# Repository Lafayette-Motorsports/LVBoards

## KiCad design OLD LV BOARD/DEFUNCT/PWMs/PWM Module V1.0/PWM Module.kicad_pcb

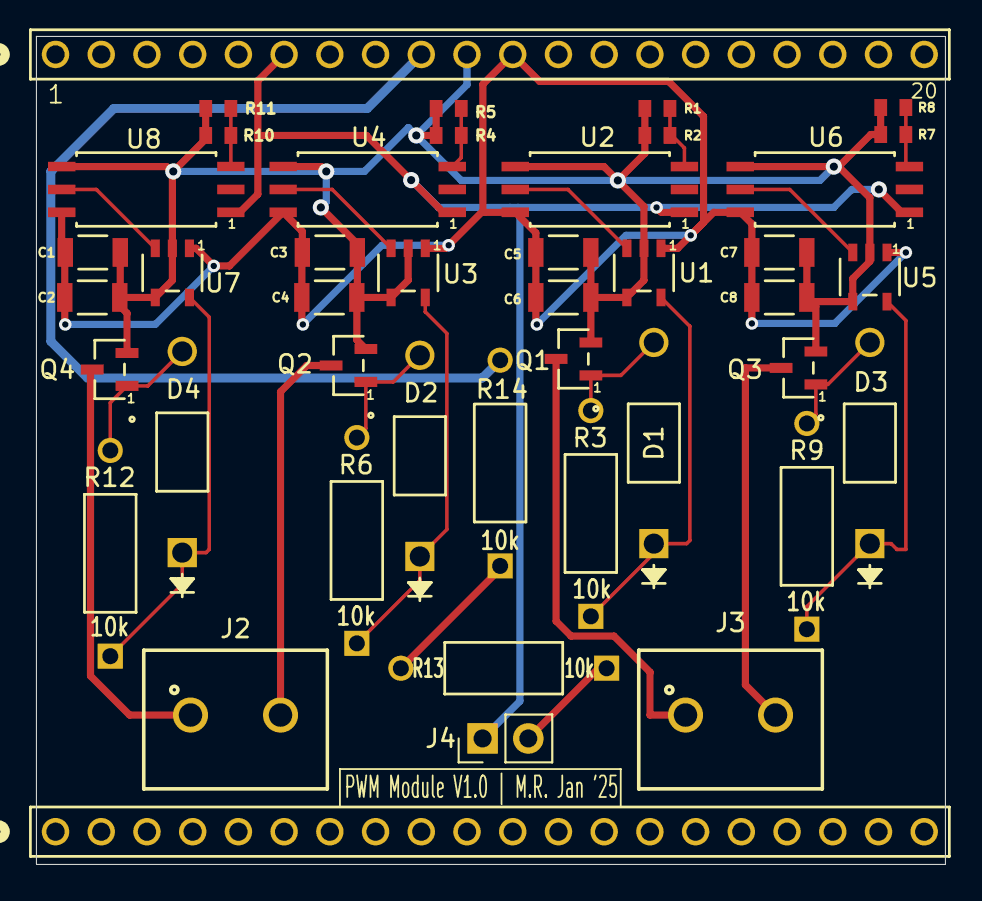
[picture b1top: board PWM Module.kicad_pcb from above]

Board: 2 copper layers, 50.5 x 46.0 mm, 43 parts (0 on the bottom side), 26 nets.

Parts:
C1, C2, C3, C4, C5, C6, C7, C8: 0.1u; CAP_CL31_SAM
D1, D2, D3, D4: 1N4001; DO-41_DIO
J2, J3: Conn_01x02_Pin; 691137710002
J4: Conn_01x02_Pin; PinHeader_1x02_P2.54mm_Vertical
J5, J5#2: PH1-20-UA; CONN_PH1-20-UA_ADM
Q1, Q2, Q3, Q4: DMN3404L-7; SOT23_DIO
R1, R2, R4, R5, R7, R8, R10, R11: 1k; STA_RMCF0603_STP
R3, R6, R9, R12, R13, R14: 10k; STA_CF14_STP
U1, U3, U5, U7: UCC27517DBVR; DBV5_TEX
U2, U4, U6, U8: TLP2745TP_E; SO6L_TOS

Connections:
GND: C1.2, C2.2, C3.2, C4.2, C5.2, C6.2, C7.2, C8.2, J5.10, Q1.2 (S), Q2.2 (S), Q3.2 (S), Q4.2 (S), R1.1, R2.1, R4.1, R5.1, R7.1, R8.1, R10.1, R11.1, U1.2 (GND), U1.4 (IN-), U2.4, U3.2 (GND), U3.4 (IN-), U4.4, U5.2 (GND), U5.4 (IN-), U6.4, U7.2 (GND), U7.4 (IN-), U8.4
unnamed: D1.2 (A), Q1.1 (G), R3.2
unnamed: D1.1 (K), R3.1, U1.5 (OUT)
unnamed: D2.2 (A), Q2.1 (G), R6.2
unnamed: D2.1 (K), R6.1, U3.5 (OUT)
unnamed: D3.2 (A), Q3.1 (G), R9.2
unnamed: D3.1 (K), R9.1, U5.5 (OUT)
unnamed: D4.2 (A), Q4.1 (G), R12.2
unnamed: D4.1 (K), R12.1, U7.5 (OUT)
unnamed: J2.1, Q4.3 (D)
unnamed: J2.2, Q2.3 (D)
unnamed: J3.1, Q1.3 (D)
unnamed: J3.2, Q3.3 (D)
unnamed: J4.1, J5.6, U2.1, U4.1, U6.1, U8.1
unnamed: J4.2, R13.1
unnamed: J5.9, R14.2
unnamed: R1.2, R2.2, U2.3
unnamed: R4.2, R5.2, U4.3
unnamed: R7.2, R8.2, U6.3
unnamed: R10.2, R11.2, U8.3
unnamed: R13.2, R14.1
unnamed: U1.3 (IN+), U2.5
unnamed: C1.1, C2.1, C3.1, C4.1, C5.1, C6.1, C7.1, C8.1, J5.11, U1.1 (VDD), U2.6, U3.1 (VDD), U4.6, U5.1 (VDD), U6.6, U7.1 (VDD), U8.6
unnamed: U3.3 (IN+), U4.5
unnamed: U5.3 (IN+), U6.5
unnamed: U7.3 (IN+), U8.5

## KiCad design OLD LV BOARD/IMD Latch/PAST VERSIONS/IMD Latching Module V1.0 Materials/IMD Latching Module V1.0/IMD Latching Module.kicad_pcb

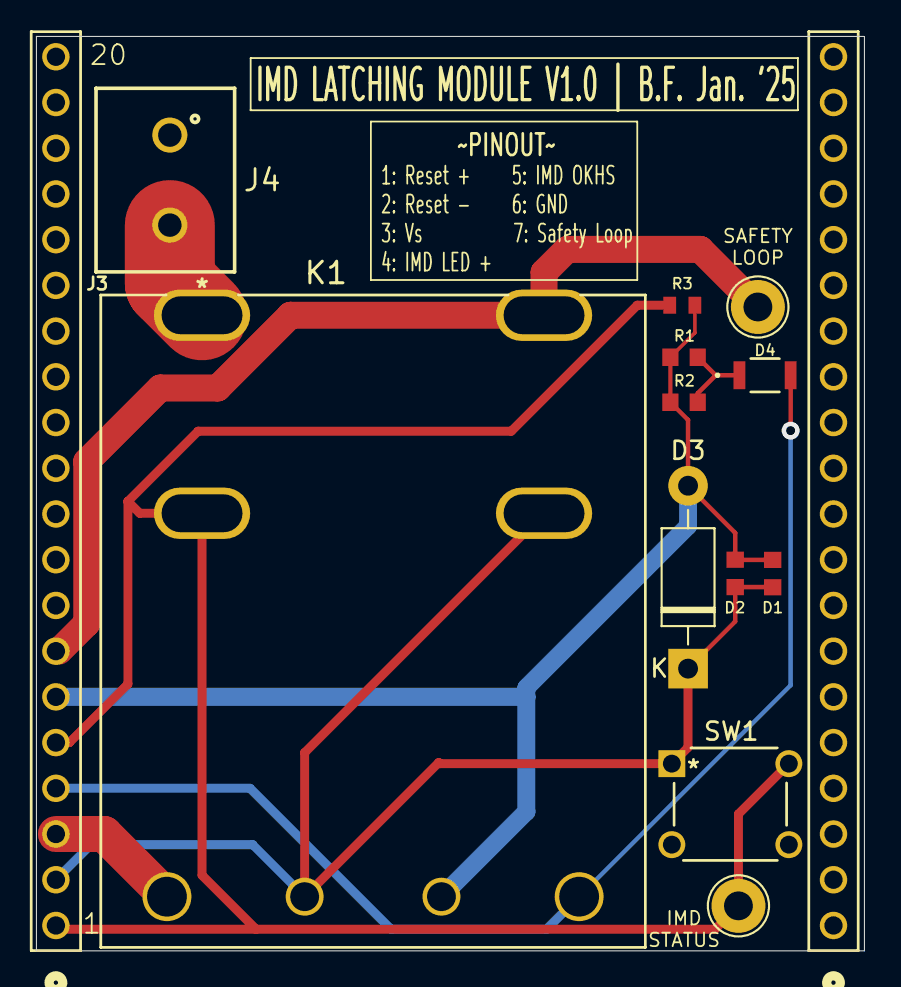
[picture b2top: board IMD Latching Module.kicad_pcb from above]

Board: 2 copper layers, 46.0 x 50.8 mm, 14 parts (0 on the bottom side), 8 nets.

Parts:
D1, D2: D_Zener; RESC1508X55N
D3: 1N4001; D_DO-41_SOD81_P10.16mm_Horizontal
D4: LED (Test); LED_AP3216SYD_KNB-L
J2, J3: PH1-20-UA; CONN_PH1-20-UA_ADM
J4: 691137710002
K1: AHES4291; AHES4_PAN
R1, R2: 1k; RESC1508X55N
R3: R; STA_RMCF0603_STP
SW1: Test Reset IMD; SW4_1825910-B_TEC
TP1, TP2: TestPoint; TestPoint_Loop_D2.60mm_Drill1.6mm_Beaded

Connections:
/GND: D1.2 (A), D2.2 (A), D3.2 (A), J3.6, K1.5, R1.1, R2.1, R3.2
/Vs: J3.3, K1.3
unnamed: D1.1 (K), D2.1 (K), D3.1 (K), J3.2, K1.4, K1.7, SW1.1
unnamed: D4.2 (A), J3.4, K1.6
unnamed: D4.1 (K), R1.2, R2.2
unnamed: J3.1, J3.5, K1.2, R3.1, SW1.2, TP1.1
unnamed: J3.7, K1.8, TP2.1
unnamed: J4.2, K1.1

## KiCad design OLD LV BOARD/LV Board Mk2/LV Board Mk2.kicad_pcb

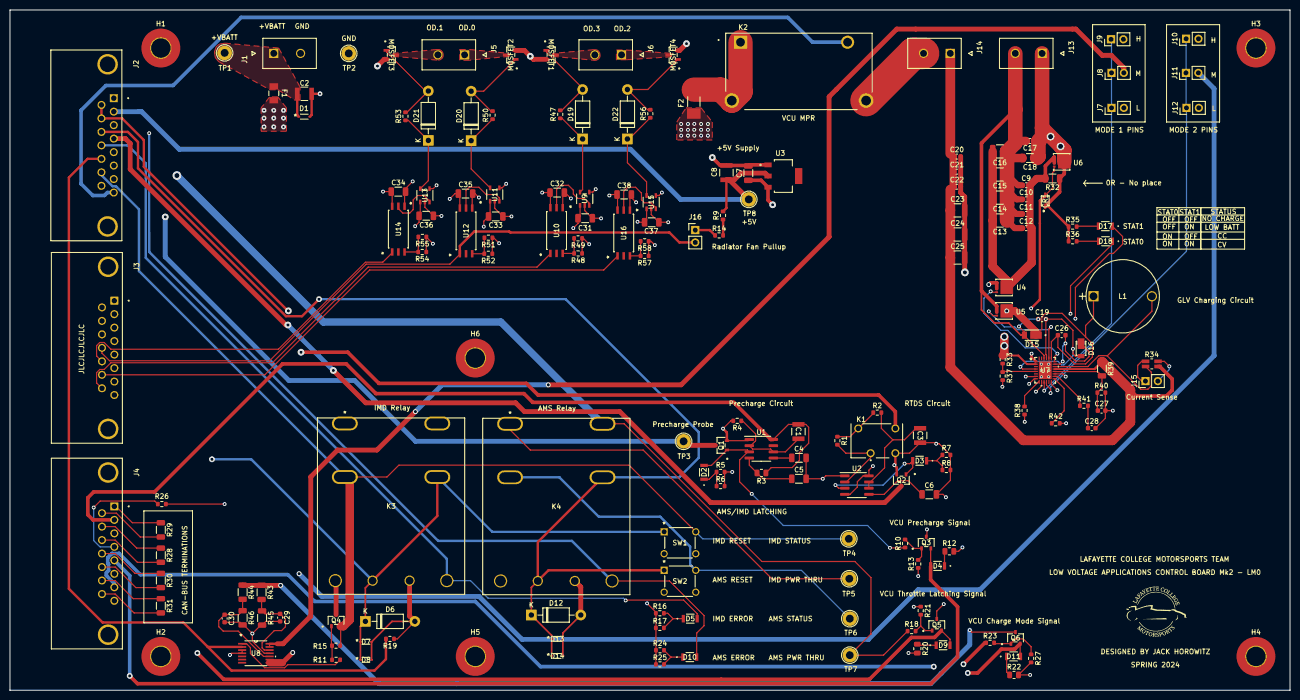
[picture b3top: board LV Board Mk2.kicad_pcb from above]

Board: 4 copper layers, 263.0 x 139.8 mm, 184 parts (0 on the bottom side), 108 nets.

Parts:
C1, C2, C3, C8: 47u; CAP_CL32_SAM
C4, C5, C6, C18, C31, C32, C33, C34, C35, C36, C37, C38: 0.1u; C_1206_3216Metric
C7: 10u; C_1206_3216Metric
C9, C10, C11, C12, C17, C19: 4.7u; C_0603_1608Metric
C13, C14, C15, C16: 47u; C_1210_3225Metric
C20, C21, C22: 22u; C_0603_1608Metric
C23, C24, C25: 100u; C_1210_3225Metric
C26: 0.22u; C_0603_1608Metric
C27, C29, C30: 0.1n; C_0603_1608Metric
C28: 27n; C_0603_1608Metric
CR1: ESD12VD3B-TP; ZENER_Pair_15-5V_clamp
D1: BZV55B15; SOD323F_DIO
D2, D3, D4, D5, D9, D10, D11, D17, D18: LED (Test); Test-Yellow LED
D6, D12, D19, D20, D21, D22: 1N4001; D_DO-41_SOD81_P10.16mm_Horizontal
D7, D8, D13, D14: D_Zener; IMD_ZENER
D15: DFLS1100-7; DIO_DFLS1100-7
D16: DFLS160Q-7; POWERDI-123
F1: C1Q 2A; C1_BEL
F2: 20A; FUSC6125X279N
H1, H2, H3, H4, H5, H6: MountingHole_Pad; MountingHole_4mm_Pad_TopBottom
J1, J5, J6, J13, J14: Conn_01x02_Pin; MOLEX_460150202
J2, J3, J4: L717SDA15P1ACH4F; AMPHENOL_L717SDA15P1ACH4F
J7, J8, J9, J10, J11, J12, J15: Conn_01x02; PinHeader_1x02_P2.54mm_Vertical
J16: Conn_01x02_Pin; PinHeader_1x02_P2.54mm_Vertical
K1: G6L-1P_DC5; RELAY_G6L-1P_DC5
K2: ALF1PF12; RELAY_ALF1PF12
K3, K4: AHES4291; AHES4_PAN
L1: 6.2u; glv_charge_inductor
MOSFET1, MOSFET2, MOSFET3, MOSFET4: DMN3404L-7; fan_driver
Q1, Q2, Q3, Q4, Q5, Q6: AON6411; SOT23_INF
R1, R9, R10, R11, R13, R14, R15, R18, R21, R23, R27, R47, R50, R53, R56: 10k; R_0603_1608Metric
R2, R4: 57.6k; R_0603_1608Metric
R3: 22k; R_0805_2012Metric
R5, R6, R7, R8, R16, R17, R24, R25, R48, R49, R51, R52, R54, R55, R57, R58: 1k; R_0603_1608Metric
R12, R20, R22: 150R; R_0805_2012Metric
R19: 2.2k; R_0603_1608Metric
R26: 3.01k; R_0603_1608Metric
R28, R29, R30, R31: 120; R_1206_3216Metric
R32: 0R; R_1206_3216Metric
R33: 50k; R_0603_1608Metric
R34: LVK12R010CER; 10m_sense
R35, R36: 12k; R_0603_1608Metric
R37, R42: 549k; R_0603_1608Metric
R38: 86.6k; R_0603_1608Metric
R39, R43, R44: 500k; R_1206_3216Metric
R40: 113k; R_0603_1608Metric
R41: 2.91k; R_0603_1608Metric
R45, R46: 215k; R_1206_3216Metric
SW1: Test Reset IMD; SW4_1825910-B_TEC
SW2: Test Reset AMS; SW4_1825910-B_TEC
TP1, TP2, TP3, TP4, TP5, TP6, TP7, TP8: TestPoint; TestPoint_Loop_D2.60mm_Drill1.6mm_Beaded
U1, U2: NE555D; SOIC-8_3.9x4.9mm_P1.27mm
U3: LT1117-5.0; REG_LT1117IST-5#PBF
U4, U5, U6: SI7116DN-T1-E3; MOSFET_INFET
U7: LTC4013EUFD-TRPBF; UFD_28_ADI
U8: LM324PWR
U9, U11, U13, U15: UCC27517DBVR; DBV5_TEX
U10, U12, U14, U16: TLP2745TP_E; motorsports_senior_design_opto

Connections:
+5V: C8.1, J2.02, Q3.3 (D), Q5.3 (D), Q6.3 (D), R9.2, R43.1, R44.1, TP8.1, U3.2 (VO)
+12V: C2.1, D1.1 (K), F1.1, F2.1, J1.1, K3.1, TP1.1
/1Out: R11.2, U8.1 (1OUT)
/GLV Charging Circuit/+15V: C17.1, C18.1, CR1.1, J13.1, R32.1, R33.1, R35.1, R36.1, U6.5 (D), U7.2 (DCIN)
/GLV Charging Circuit/GLV_Charge: C20.1, C21.1, C22.1, C23.1, C24.1, C25.1, J14.1, R34.3, R39.1, U7.19 (BAT)
/GLV Charging Circuit/INTVcc: C19.2, D16.A, J9.2, J10.2, U7.4 (FBOC), U7.17 (NTC), U7.25 (INTVCC)
/GLV Charging Circuit/REF: C9.1, C10.1, C11.1, C12.1, C13.1, C14.1, C15.1, C16.1, C17.2, C18.2, C19.1, D15.A, J13.2, U5.1 (S), U5.2 (S), U5.3 (S), U7.26 (PGND)
/GLV Charging Circuit/mode1: J7.1, J8.1, J9.1, U7.11 (MODE1)
/GLV Charging Circuit/mode2: J10.1, J11.1, J12.1, U7.12 (MODE2)
/IMD_Okhs: J2.13, R19.2, U8.2 (1IN-)
/PWM Driver Circuit1/Lowside Drive: J5.2, MOSFET3.3 (D)
/PWM Driver Circuit1/Vpwm: J3.13, U14.1
/PWM Driver Circuit2/Lowside Drive: J6.1, MOSFET4.3 (D)
/PWM Driver Circuit2/Vpwm: J3.14, U16.1
/PWM Driver Circuit3/Lowside Drive: J6.2, MOSFET1.3 (D)
/PWM Driver Circuit3/Vpwm: J3.15, U10.1
/PWM Driver Circuit/Lowside Drive: J5.1, MOSFET2.3 (D)
/PWM Driver Circuit/Vpwm: J3.12, J16.2, U12.1
/TSMS Vs: C1.1, J4.02, R3.1, U1.8 (VCC)
/VCU VBATT: J14.2, K2.4
GND: C2.2, C3.2, C4.2, C5.2, C6.2, C7.2, C8.2, C20.2, C21.2, C22.2, C23.2, C24.2, C25.2, C27.2, C28.2, C29.2, C30.2, C31.2, C32.2, C33.2, C34.2, C35.2, C36.2, C37.2, C38.2, D1.2 (A), D6.2 (A), D7.2 (A), D8.2 (A), D12.2 (A), D13.2 (A), D14.2 (A), H1.1, H2.1, H3.1, H4.1, H5.1, H6.1, J1.2, J2.S2 (SHIELD), J3.S2 (SHIELD), J4.S2 (SHIELD), J7.2, J12.2, K1.4, K3.5, K4.5, MOSFET1.2 (S), MOSFET2.2 (S), MOSFET3.2 (S), MOSFET4.2 (S), Q1.2 (S), Q2.2 (S), R4.2, R5.2, R6.2, R7.2, R8.2, R12.2, R13.1, R16.1, R17.1, R19.1, R20.2, R21.1, R22.2, R24.1, R25.1, R27.2, R37.2, R38.1, R40.2, R42.2, R45.2, R46.2, R48.1, R49.1, R51.1, R52.1, R54.1, R55.1, R57.1, R58.1, TP2.1, U1.1 (GND), U2.1 (GND), U3.1 (GND), U7.10 (TMR), U7.14 (SYNC), U7.29 (SGND), U8.11 (GND), U9.2 (GND), U9.4 (IN-), U10.4, U11.2 (GND), U11.4 (IN-), U12.4, U13.2 (GND), U13.4 (IN-), U14.4, U15.2 (GND), U15.4 (IN-), U16.4
unnamed: C28.1, R41.2
unnamed: D2.2 (A), Q1.1 (G), R10.1, U1.3 (Q)
unnamed: D2.1 (K), R5.1, R6.1
unnamed: D3.2 (A), Q2.1 (G), U2.3 (Q)
unnamed: D3.1 (K), R7.1, R8.1
unnamed: D4.2 (A), J4.05, Q3.2 (S)
unnamed: D4.1 (K), R12.1
unnamed: D5.2 (A), J2.12, K3.6
unnamed: D5.1 (K), R16.2, R17.2
unnamed: D6.1 (K), D7.1 (K), D8.1 (K), J2.15, K3.4, K3.7, SW1.1
unnamed: D9.2 (A), J4.06, Q5.2 (S)
unnamed: D9.1 (K), R20.1
unnamed: D10.2 (A), J2.01, K4.6
unnamed: D10.1 (K), R24.2, R25.2
unnamed: D11.2 (A), J4.07, Q6.2 (S)
unnamed: D11.1 (K), R22.1
unnamed: D12.1 (K), D13.1 (K), D14.1 (K), J2.11, K4.4, K4.7, SW2.1
unnamed: D17.2 (A), R35.2
unnamed: D17.1 (K), U7.8 (STAT1)
unnamed: D18.2 (A), R36.2
unnamed: D18.1 (K), U7.7 (STAT0)
unnamed: D19.2 (A), MOSFET1.1 (G), R47.2
unnamed: D19.1 (K), R47.1, U9.5 (OUT)
unnamed: D20.2 (A), MOSFET2.1 (G), R50.2
unnamed: D20.1 (K), R50.1, U11.5 (OUT)
unnamed: D21.2 (A), MOSFET3.1 (G), R53.2
unnamed: D21.1 (K), R53.1, U13.5 (OUT)
unnamed: D22.2 (A), MOSFET4.1 (G), R56.2
unnamed: D22.1 (K), R56.1, U15.5 (OUT)
unnamed: F2.2, K2.1, K2.3
unnamed: J2.03, K4.8, R18.1, TP7.1
unnamed: J2.06, K1.5
unnamed: J2.08, K2.2
unnamed: J2.09, J2.10, K4.2, SW2.2, TP6.1
unnamed: J4.01, R29.1
unnamed: J4.04, R26.2
unnamed: J4.08, R23.1
unnamed: J4.09, R29.2
unnamed: J4.10, R28.1
unnamed: J4.11, R28.2
unnamed: J4.12, R30.1
unnamed: J4.13, R30.2
unnamed: J4.14, R31.1
unnamed: J4.15, R31.2
unnamed: J8.2, U8.13 (4IN-), U8.14 (4OUT)
unnamed: J11.2, U8.8 (3OUT), U8.9 (3IN-)
unnamed: J15.1, R34.1
unnamed: J15.2, R34.4
unnamed: J16.1, R14.1
unnamed: K3.8, K4.1, TP5.1
unnamed: J2.07, Q1.3 (D), TP3.1
unnamed: J2.04, Q2.3 (D)
unnamed: Q3.1 (G), R10.2, R13.2
unnamed: Q4.1 (G), R11.1, R15.2
unnamed: J2.14, K3.2, Q4.2 (S), R15.1, SW1.2, TP4.1
unnamed: Q5.1 (G), R18.2, R21.2
unnamed: Q6.1 (G), R23.2, R27.1
unnamed: R9.1, R14.2
unnamed: R48.2, R49.2, U10.3
unnamed: R51.2, R52.2, U12.3
unnamed: R54.2, R55.2, U14.3
unnamed: R57.2, R58.2, U16.3
unnamed: C4.1, U1.5 (CV)
unnamed: C5.1, R3.2, U1.4 (R)
unnamed: C1.2, R4.1, U1.2 (TR), U1.6 (THR)
unnamed: C6.1, U2.5 (CV)
unnamed: C3.1, R2.2, U2.6 (THR), U2.7 (DIS)
unnamed: K1.2, R1.2, U2.2 (TR)
unnamed: C9.2, C10.2, C11.2, C12.2, C13.2, C14.2, C15.2, C16.2, R32.2, U4.5 (D), U6.1 (S), U6.2 (S), U6.3 (S)
unnamed: U4.4 (G), U7.22 (TG)
unnamed: C26.1, D15.K, L1.1, U4.1 (S), U4.2 (S), U4.3 (S), U5.5 (D), U7.23 (SW)
unnamed: U5.4 (G), U7.24 (BG)
unnamed: CR1.2, U6.4 (G), U7.1 (INFET)
unnamed: C26.2, D16.C, U7.21 (BST)
unnamed: R33.2, R37.1, U7.5 (ENAB)
unnamed: C27.1, R39.2, R40.1, U7.18 (FB)
unnamed: R41.1, U7.16 (ITH)
unnamed: R38.2, U7.9 (LB)
unnamed: R42.1, U7.15 (RT)
unnamed: L1.2, R34.2, U7.20 (SENSE)
unnamed: C30.1, R44.2, R46.1, U8.10 (3IN+)
unnamed: C29.1, R43.2, R45.1, U8.12 (4IN+)
unnamed: U9.3 (IN+), U10.5
unnamed: U11.3 (IN+), U12.5
unnamed: U13.3 (IN+), U14.5
unnamed: U15.3 (IN+), U16.5
VS: C7.1, C31.1, C32.1, C33.1, C34.1, C35.1, C36.1, C37.1, C38.1, F1.2, K1.8, K3.3, K4.3, Q4.3 (D), R1.1, R2.1, R26.1, U2.4 (R), U2.8 (VCC), U3.3 (VI), U8.3 (1IN+), U8.4 (VCC), U9.1 (VDD), U10.6, U11.1 (VDD), U12.6, U13.1 (VDD), U14.6, U15.1 (VDD), U16.6

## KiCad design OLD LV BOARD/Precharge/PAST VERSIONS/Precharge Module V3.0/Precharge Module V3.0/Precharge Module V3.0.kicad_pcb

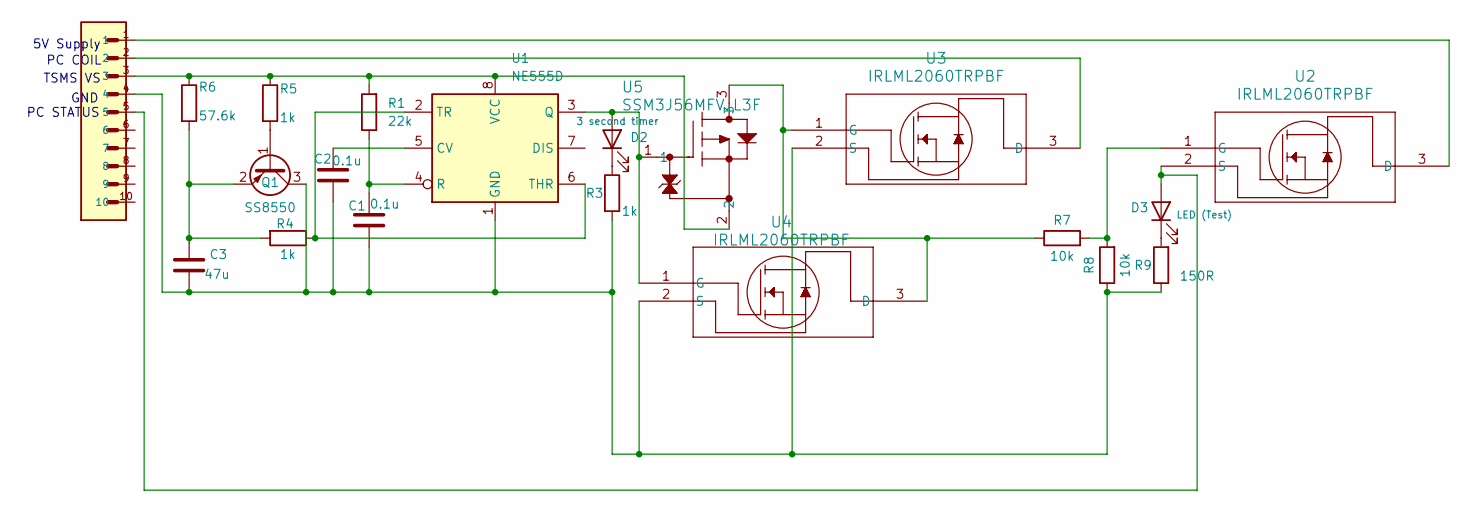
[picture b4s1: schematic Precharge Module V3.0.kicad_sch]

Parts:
C1, C2: 0.1u; CAP_CL31_SAM
C3: 47u; CAP_CL32_SAM
D2: 3 second timer; LED_AP3216SYD_KNB
D3: LED (Test); LED_AP3216SYD_KNB
J1: PH1-10-UA; 1X10-2.54MM-THT
Q1: SS8550; SOT-23_MCC
R1: 22k; STA_RMCF0805_STP
R3, R4, R5: 1k; STA_RMCF0603_STP
R6: 57.6k; STA_CF14_STP
R7, R8: 10k; STA_CF14_STP
R9: 150R; RC0805N_YAG
U1: NE555D; SOIC127P599X175-8N
U2, U3, U4: IRLML2060TRPBF; SOT23_INF
U5: SSM3J56MFV_L3F; VESM_TOS

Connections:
unnamed: D2.2 (A), U1.3 (Q), U4.1 (G), U5.1
unnamed: D2.1 (K), R3.1
unnamed 2: D3.2 (A), J1.5, U2.2 (S); also elsewhere on the board
unnamed: D3.1 (K), R9.2
unnamed: Q1.1 (B), R5.2
unnamed: C1.2, C2.2, C3.2, J1.4, Q1.3 (C), R3.2, R8.1, R9.1, U1.1 (GND), U3.2 (S), U4.2 (S)
unnamed: C3.1, Q1.2 (E), R4.2, R6.2
unnamed: C2.1, U1.5 (CV)
unnamed: C1.1, R1.1, U1.4 (R)
unnamed: R4.1, U1.2 (TR), U1.6 (THR)
unnamed: J1.3, R1.2, R5.1, R6.1, U1.8 (VCC), U5.2
unnamed: J1.1, U2.3 (D)
unnamed: R7.2, R8.2, U2.1 (G)
unnamed: J1.2, U3.3 (D)
unnamed: R7.1, U3.1 (G), U4.3 (D), U5.3

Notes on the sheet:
GND
PC COIL
TSMS VS
PC STATUS
5V Supply

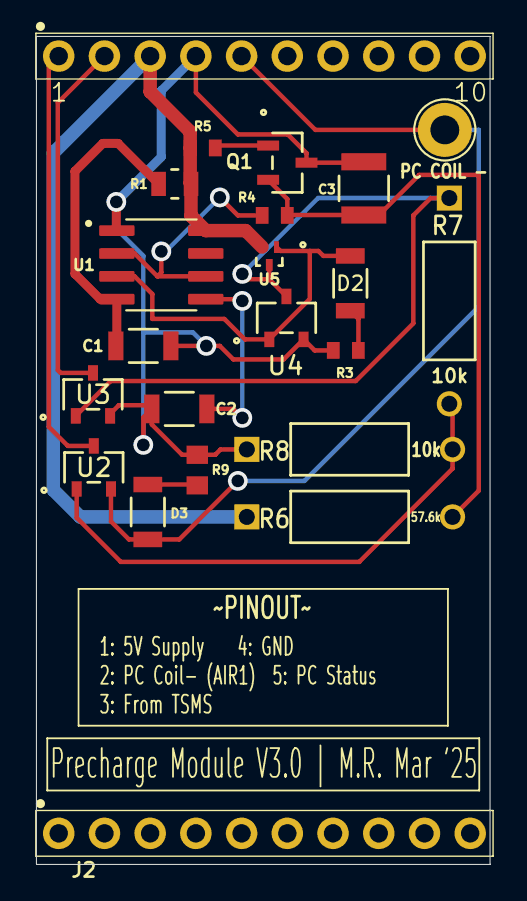
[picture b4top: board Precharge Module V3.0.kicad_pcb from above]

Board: 2 copper layers, 25.2 x 46.0 mm, 22 parts (0 on the bottom side), 15 nets.

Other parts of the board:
J2: PH1-10-UA; 1X10-2.54MM-THT
PC COIL -: TestPoint; TestPoint_Loop_D2.60mm_Drill1.6mm_Beaded

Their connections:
unnamed 2: PC COIL -.1; also elsewhere on the board

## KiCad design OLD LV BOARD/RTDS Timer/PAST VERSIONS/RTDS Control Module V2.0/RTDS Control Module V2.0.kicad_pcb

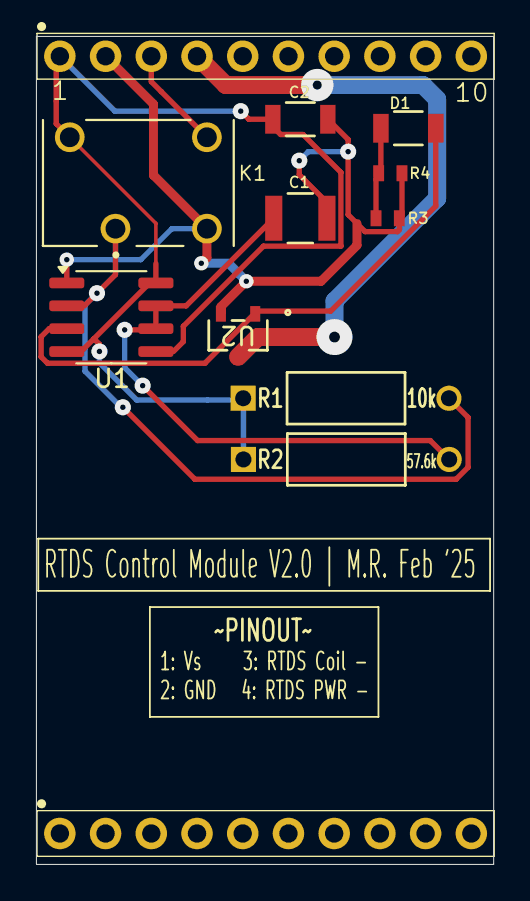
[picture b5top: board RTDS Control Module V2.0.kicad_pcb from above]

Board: 2 copper layers, 25.4 x 46.0 mm, 12 parts (0 on the bottom side), 8 nets.

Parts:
C1: 47u; CAP_CL32_SAM
C2: 0.1u; CAP_CL31_SAM
D1: LED (Test); LED_AP3216SYD_KNB
J1, J1#2: PH1-10-UA; 1X10-2.54MM-THT
K1: G6L-1P_DC5; RELAY_G6L-1P_DC5
R1: 10k; STA_CF14_STP
R2: 57.6k; STA_CF14_STP
R3, R4: 1k; STA_RMCF0603_STP-L
U1: NE555D; SOIC-8_3.9x4.9mm_P1.27mm
U2: IRLML2060TRPBF; SOT23_INF

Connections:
/GND: C1.2, C2.2, J1#2.2, K1.4, R3.2, R4.2, U1.1 (GND), U2.2 (S)
/Vs: C2.1, J1#2.1, K1.8, R1.1, R2.1, U1.4 (R), U1.5 (CV), U1.8 (VCC)
unnamed: D1.2 (A), U1.3 (Q), U2.1 (G)
unnamed: D1.1 (K), R3.1, R4.1
unnamed: J1#2.3, K1.5
unnamed: C1.1, R2.2, U1.6 (THR), U1.7 (DIS)
unnamed: K1.2, R1.2, U1.2 (TR)
unnamed: J1#2.4, U2.3 (D)

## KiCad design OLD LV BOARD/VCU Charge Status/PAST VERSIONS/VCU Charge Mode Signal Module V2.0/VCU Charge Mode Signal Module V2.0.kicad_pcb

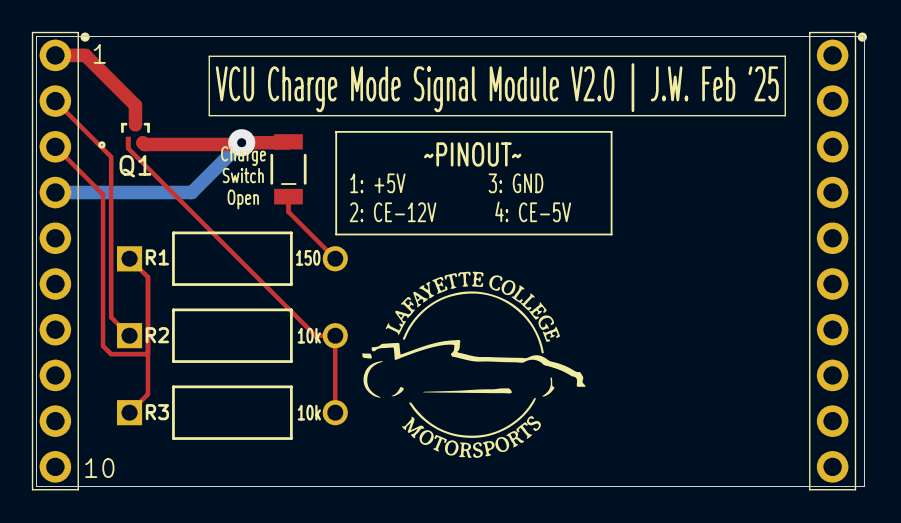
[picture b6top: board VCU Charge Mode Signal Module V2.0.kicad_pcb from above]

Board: 2 copper layers, 46.0 x 25.0 mm, 7 parts (0 on the bottom side), 6 nets.

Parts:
D1: LED (Test); LED_AP3216SYD_KNB
J1, J1#2: PH1-10-UA; 1X10-2.54MM-THT
Q1: SSM3J56MFV; VESM_TOS
R1: 150R; STA_CF14_STP
R2, R3: 10k; STA_CF14_STP

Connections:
unnamed: D1.2 (A), J1.4, Q1.2 (S)
unnamed: D1.1 (K), R1.2
unnamed: J1.2, R2.1
unnamed: J1.3, R1.1, R3.1
unnamed: J1.1, Q1.3 (D)
unnamed: Q1.1 (G), R2.2, R3.2

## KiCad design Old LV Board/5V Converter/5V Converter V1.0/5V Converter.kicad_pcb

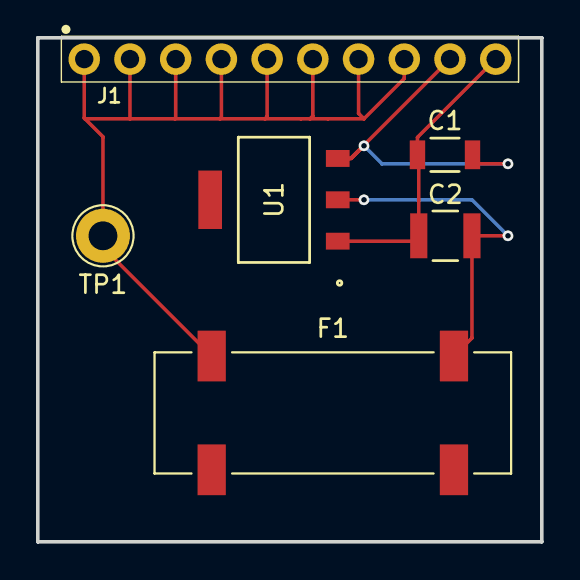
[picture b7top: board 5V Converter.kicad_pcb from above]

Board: 2 copper layers, 28.0 x 28.0 mm, 6 parts (0 on the bottom side), 4 nets.

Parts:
C1: 10u; CAP_CL31_SAM
C2: 47u; CAP_CL32_SAM
F1: 3587TR; FUSE_3587TR
J1: PH1-10-UA; 1X10-2.54MM-THT
TP1: TestPoint; TestPoint_Loop_D2.60mm_Drill1.6mm_Beaded
U1: LT1117-5.0; SOT-223_ST_LIT-M

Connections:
/GND: C1.2, C2.2, J1.10, U1.1 (GND)
/Vs: C1.1, J1.9, U1.3 (VI)
unnamed: F1.1_1, J1.1, J1.2, J1.3, J1.4, J1.5, J1.6, J1.7, J1.8, TP1.1
unnamed: C2.1, F1.2_1, U1.2 (VO)
